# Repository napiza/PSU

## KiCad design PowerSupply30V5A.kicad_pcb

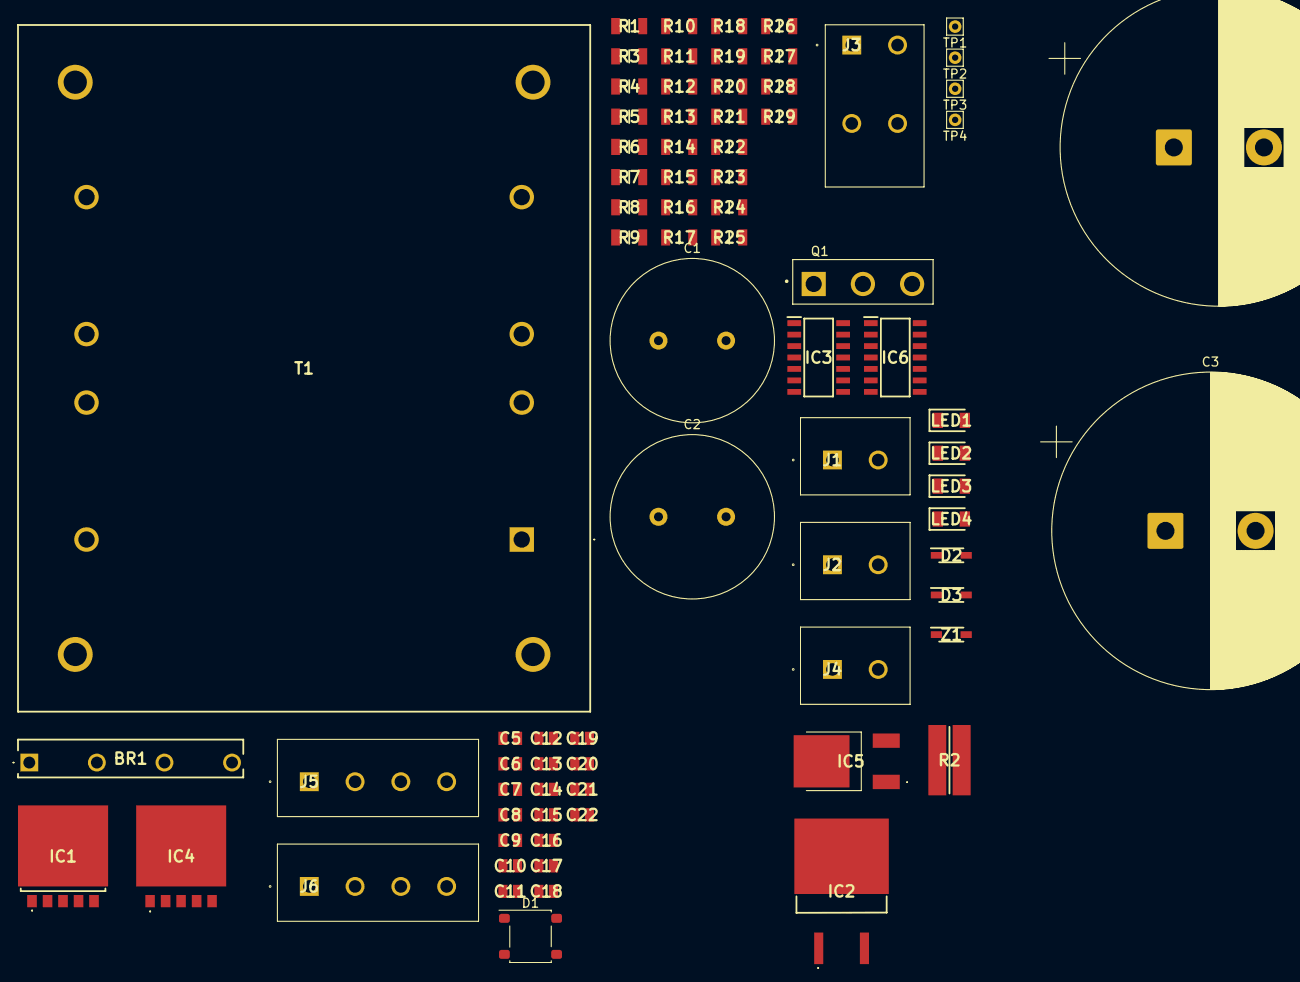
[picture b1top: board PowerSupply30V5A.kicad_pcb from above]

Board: 2 copper layers, 78 parts (0 on the bottom side), 28 nets, no tracks yet.

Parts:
BR1: KBJB1506_T0_00301
C1, C2: 1000uF; C_Radial_D18.0mm_H35.5mm_P7.50mm
C3, C4: 12000uF; CP_Radial_D35.0mm_P10.00mm_SnapIn
C5, C10, C11, C12, C14, C17, C22: 1μF_25V; CAPC2012X94N
C6, C15: 330nF_25V; CAPC2012X94N
C7, C8, C13, C16, C21: 100nF_50V; CAPC2012X94N
C9, C20: 4.7uF_25V; CAPC2012X94N
C18, C19: 4.7nF_50V; CAPC2012X94N
D1: Bridge_1ph; P34_SO-DIL-ABS
D2, D3: 1N4150W-E3-18; SOD3716X135N
IC1: BDJ5FD0WHFP-TR; BDJ5FD0WHFPTR
IC2: MC7915BD2TR4G
IC3, IC6: LF247DT; SOIC127P600X175-14N
IC4: BDJ2FD0WHFP-TR; BDJ2FD0WHFPTR
IC5: MC7805BDTRKG; LM317MADTRKG
J1, J2, J4: 1755736
J3: 1017503
J5, J6: 1755752
LED1, LED2, LED3, LED4: CMD15-21VGD_TR8; LEDC3215X130N
Q1: IRFP460; TO546P1587X531X2511-3
R1, R3, R9, R12, R13, R19: 10kΩ; RESC3216X60N
R2: FCSL76R050DER; RESC3876X70N
R4, R5, R17, R18, R20, R21, R23, R24: 100kΩ; RESC3216X60N
R6, R7: 8.2kΩ; RESC3216X60N
R8, R10: 180kΩ; RESC3216X60N
R11, R15: 18kΩ; RESC3216X60N
R14, R16: 0Ω; RESC3216X60N
R22: 22kΩ; RESC3216X60N
R25: 100Ω; RESC3216X60N
R26, R27: 620Ω; RESC3216X60N
R28: 470Ω; RESC3216X60N
R29: 130Ω; RESC3216X60N
T1: 14A-56-28; 14A5628
TP1, TP2, TP3, TP4: TestPoint; Pin_D0.7mm_L6.5mm_W1.8mm_FlatFork
Z1: 6V; SOD3716X135N

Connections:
0V_IN: BR1.4 (-), C1.2, C2.2, J3.3, J3.4
30V_IN: BR1.1 (+), C1.1, Q1.2
+5V: IC5.3 (OUT), J5.4, TP3.1
+12V: IC4.4 (VO), IC5.1 (IN), J4.1, TP4.1, Z1.1 (K)
+15V: IC1.4 (VO), IC3.4 (V+), IC4.1 (CTL), IC4.2 (VCC), IC6.4 (V+), TP1.1
-15V: IC2.3 (OUT), IC3.11 (V-), IC6.11 (V-), TP2.1
ANALOGUE_OV: C3.2, C4.1, IC1.3 (GND), IC1.6 (FIN), IC2.1 (GND), IC4.3 (GND), IC4.5 (N.C._), IC4.6 (FIN), IC5.2 (GND), J4.2, J5.1, J6.2, J6.4, LED1.2 (A), LED2.1 (K), LED3.2 (A), LED4.2 (A), Q1.3, R2.1, T1.9, T1.10
I_MEAS: IC3.1, IC6.10 (+)
I_OUT_MEAS-: C2.1, J3.1, J3.2, R2.2
I_REFERENCE: IC6.1, IC6.2 (-)
I_control: D3.1 (K), IC3.8
unnamed: BR1.2 (~_1), J2.2
unnamed: BR1.3 (~_2), J2.1
unnamed: C4.2, D1.2 (-), IC2.2 (IN)
unnamed: C3.1, C5.2, D1.1 (+), IC1.1 (CTL), IC1.2 (VCC)
unnamed: D1.3, T1.7
unnamed: D1.4, T1.12
unnamed: IC6.3 (+), J5.3
unnamed: IC6.5 (+), J5.2
unnamed: IC6.8, IC6.9 (-), J6.1
unnamed: IC6.13 (-), IC6.14, J6.3
unnamed: J1.1, T1.1
unnamed: J1.2, T1.6
unnamed: T1.3, T1.4
V_GATE: D2.2 (A), D3.2 (A)
V_MEAS: IC3.7, IC6.12 (+)
V_REFERENCE: IC6.6 (-), IC6.7
V_control: D2.1 (K), IC3.14

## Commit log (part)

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2026-05-25 upload files from local
